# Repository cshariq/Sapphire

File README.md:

<div align="center">

  <h1>Sapphire</h1>
  <p><b>The all-in-one mac app that redefines the notch</b></p>
  <a href="https://sapphire-app.tech" style="text-decoration: none; margin-right: 10px;">
    <div style="background-color: #007aff; color: white; padding: 10px 20px; border-radius: 8px; display: inline-block; font-weight: bold;">
      Official Website
    </div>
  </a>
  <a href="https://github.com/cshariq/Sapphire/releases/latest" style="text-decoration: none;">
    <div style="background-color: #007aff; color: white; padding: 10px 20px; border-radius: 8px; display: inline-block; font-weight: bold;">
      Download Latest Release
    </div>
  </a>
  <a href="https://discord.gg/Ryuea8vM2h" style="text-decoration: none;">
    <div style="background-color: #007aff; color: white; padding: 10px 20px; border-radius: 8px; display: inline-block; font-weight: bold;">
      Join Discord
    </div>
  </a>
</div>

<br>

Sapphire is a sleek notch app that displays current activities neatly around the notch on newer MacBooks. It also includes a suite of convenient features, from nearby share compatibility for easy file transfers to a versatile window snapping system.

## Installation

1.  **Download:** Download the latest package release from the [releases page](https://github.com/cshariq/Sapphire/releases/tag/Latest).
2.  **Install:** Open the downloaded package and follow the installation process.
3.  **Permissions:** On first launch, you may need to grant accessibility and other permissions in `System Settings` for all features to work correctly.

## Features

<div style="display: flex; flex-wrap: wrap; gap: 16px; justify-content: center;">

  <div style="border: 1px solid #30363d; border-radius: 8px; padding: 16px; width: 300px; background-color: #1c1c1e;">
    <h3 style="margin-top: 0;">Nearby Share</h3>
    <p>Allows sharing files, pictures, videos, websites, and more from Android to your mac!</p>
  </div>

  <div style="border: 1px solid #30363d; border-radius: 8px; padding: 16px; width: 300px; background-color: #1c1c1e;">
    <h3 style="margin-top: 0;">Now Playing</h3>
    <p>Displays currently playing media of all types in the notch (works with macOS 15.5 as well), and more.</p>
  </div>

  <div style="border: 1px solid #30363d; border-radius: 8px; padding: 16px; width: 300px; background-color: #1c1c1e;">
    <h3 style="margin-top: 0;">Advanced Audio Features (Beta)</h3>
    <p>Adjust individual app volumes, device volumes, app EQs and device EQs right from the notch</p>
  </div>
  
  <div style="border: 1px solid #30363d; border-radius: 8px; padding: 16px; width: 300px; background-color: #1c1c1e;">
    <h3 style="margin-top: 0;">Eye Break</h3>
    <p>Health should always be your priority. With the sleek notch UI, a reminder is given every 20 minutes to look 20 feet away for 20 seconds, and more.</p>
  </div>

  <div style="border: 1px solid #30363d; border-radius: 8px; padding: 16px; width: 300px; background-color: #1c1c1e;">
    <h3 style="margin-top: 0;">Weather</h3>
    <p>Current weather is persistently shown in the notch, so you're in the know about your surroundings, and more.</p>
  </div>

  <div style="border: 1px solid #30363d; border-radius: 8px; padding: 16px; width: 300px; background-color: #1c1c1e;">
    <h3 style="margin-top: 0;">Gemini</h3>
    <p>Share your screen and discuss topics conveniently using Gemini Live, and more.</p>
  </div>

  <div style="border: 1px solid #30363d; border-radius: 8px; padding: 16px; width: 300px; background-color: #1c1c1e;">
    <h3 style="margin-top: 0;">Calendar</h3>
    <p>See upcoming events and get alerted for ongoing events, and more.</p>
  </div>

  <div style="border: 1px solid #30363d; border-radius: 8px; padding: 16px; width: 300px; background-color: #1c1c1e;">
    <h3 style="margin-top: 0;">Lock Screen</h3>
    <p>See the weather, your music, and upcoming calendar events on your Mac's lockscreen, and more.</p>
  </div>

  <div style="border: 1px solid #30363d; border-radius: 8px; padding: 16px; width: 300px; background-color: #1c1c1e;">
    <h3 style="margin-top: 0;">File Shelf</h3>
    <p>Airdrop and store files conveniently with access to the file shelf, and more.</p>
  </div>

  <div style="border: 1px solid #30363d; border-radius: 8px; padding: 16px; width: 300px; background-color: #1c1c1e;">
    <h3 style="margin-top: 0;">Snap Zones</h3>
    <p>Snapping windows using macOS's built-in snapping tools is limited and leaves a gap between windows. Sapphire provides a versatile and customizable window snapping system, and more.</p>
  </div>

  <div style="border: 1px solid #30363d; border-radius: 8px; padding: 16px; width: 300px; background-color: #1c1c1e;">
    <h3 style="margin-top: 0;">Music</h3>
    <p>View now playing media on the notch with additional information and controls when the now playing media is expanded, and more.</p>
  </div>

  <div style="border: 1px solid #30363d; border-radius: 8px; padding: 16px; width: 300px; background-color: #1c1c1e;">
    <h3 style="margin-top: 0;">Bluetooth</h3>
    <p>Get a notice when a Bluetooth device connects to your Mac, and more.</p>
  </div>

  <div style="border: 1px solid #30363d; border-radius: 8px; padding: 16px; width: 300px; background-color: #1c1c1e;">
    <h3 style="margin-top: 0;">Caffeinate</h3>
    <p>Caffeinate your Mac with a press of a button, and more.</p>
  </div>

</div>

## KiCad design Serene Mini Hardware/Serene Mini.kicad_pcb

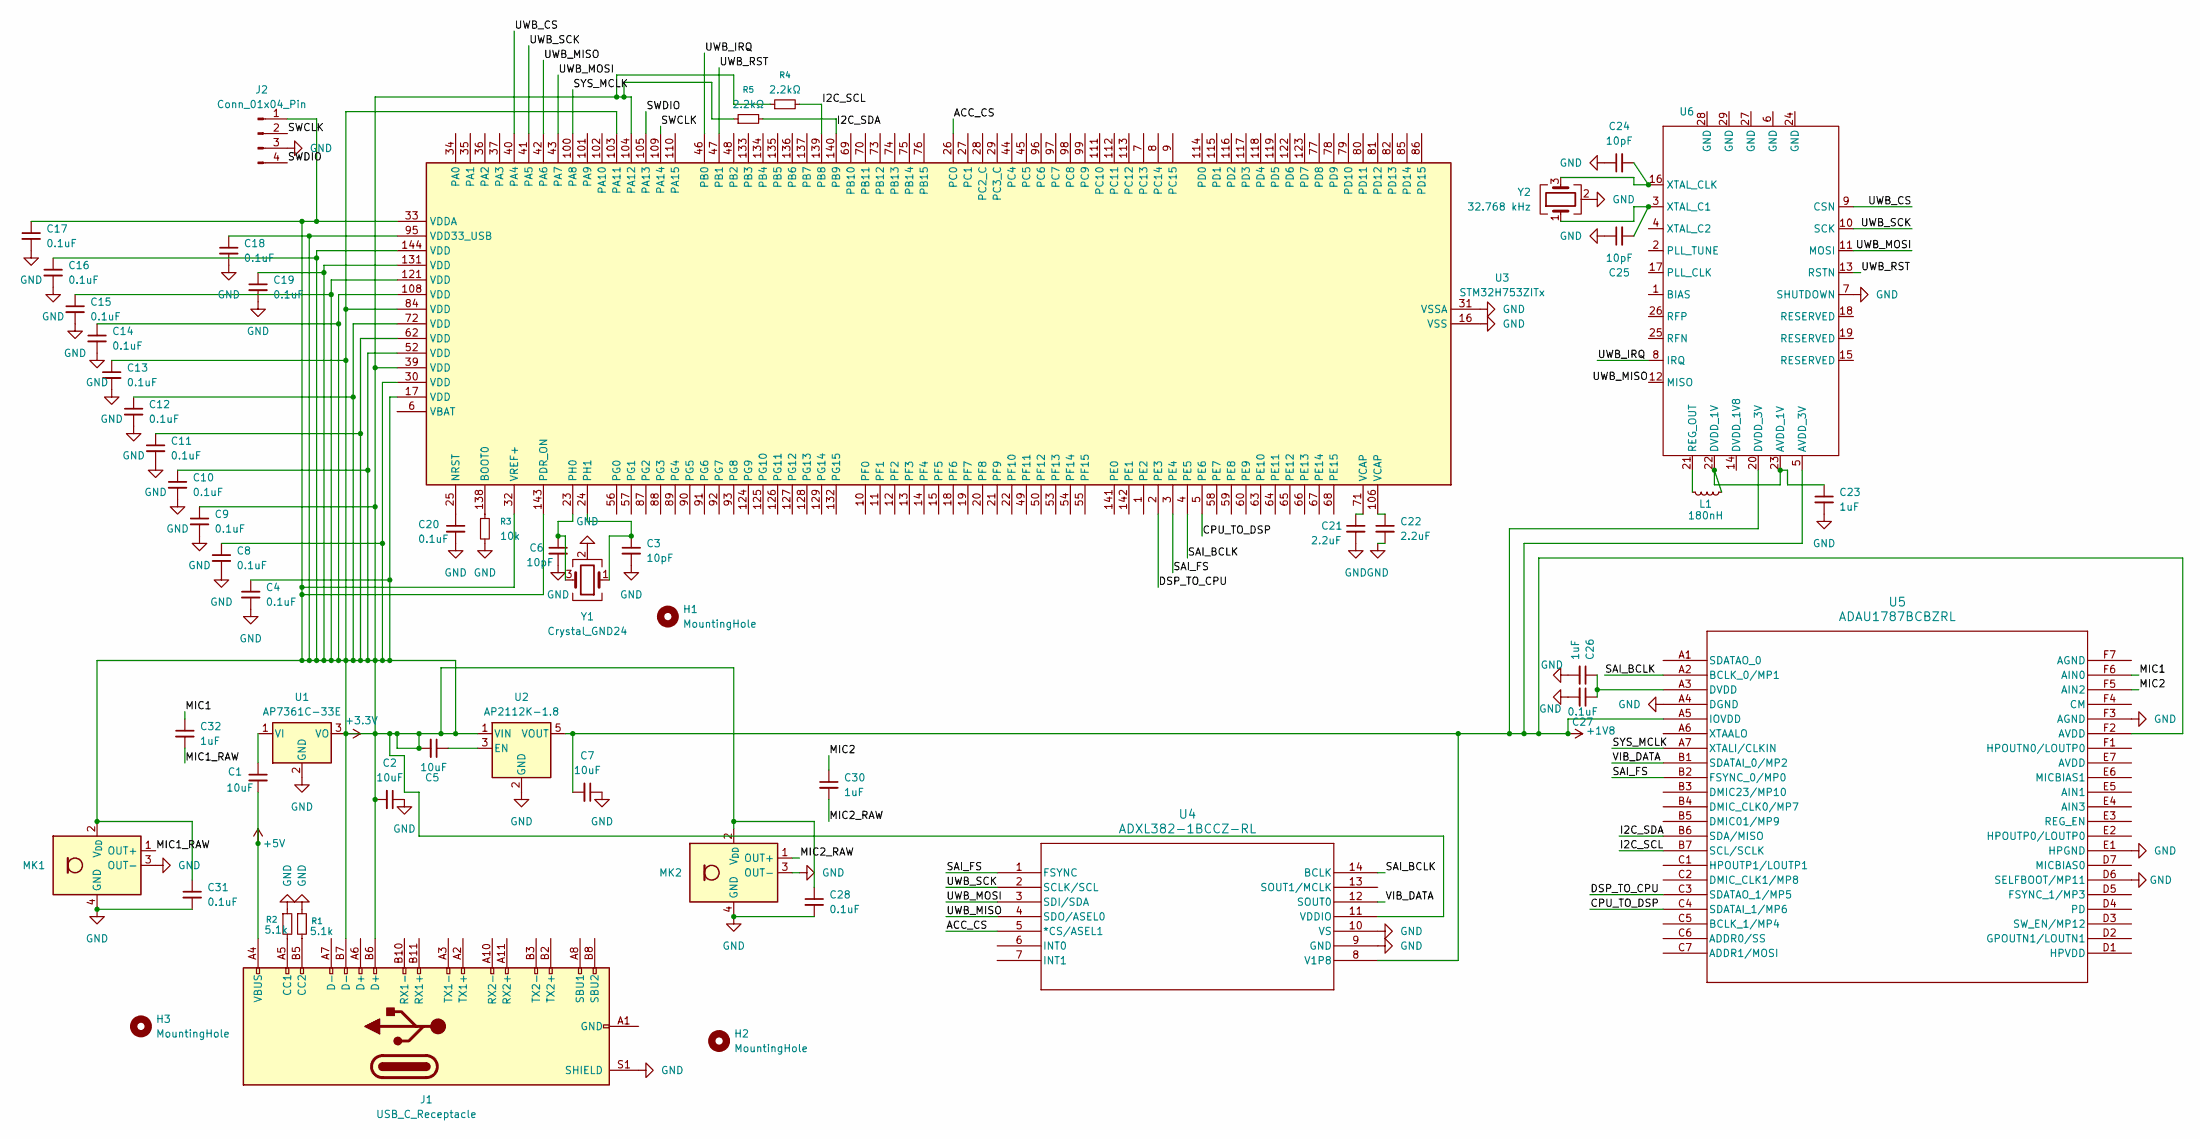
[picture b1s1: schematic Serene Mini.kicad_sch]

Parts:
C1, C2, C5, C7: 10uF; C_0402_1005Metric
C3, C6, C24, C25: 10pF; C_0402_1005Metric
C4, C8, C9, C10, C11, C12, C13, C14, C15, C16, C17, C18, C19, C20, C27, C28, C31: 0.1uF; C_0402_1005Metric
C21, C22: 2.2uF; C_0402_1005Metric
C23, C26, C30, C32: 1uF; C_0402_1005Metric
H1, H2, H3: MountingHole; MountingHole_2.2mm_M2
J1: USB_C_Receptacle; USB_C_Receptacle_Amphenol_12401548E4-2A
J2: Conn_01x04_Pin; PinHeader_1x04_P2.54mm_Vertical
L1: 180nH; L_0603_1608Metric
MK1, MK2: IM73A135V01; Infineon_PG-LLGA-5-2
R1, R2: 5.1k; R_0402_1005Metric
R3: 10k; R_0402_1005Metric
R4, R5: 2.2kΩ; R_0402_1005Metric
U1: AP7361C-33E; SOT-223-3_TabPin2
U2: AP2112K-1.8; SOT-23-5
U3: STM32H753ZITx; LQFP-144_20x20mm_P0.5mm
U4: ADXL382-1BCCZ-RL; ADXL382_Ultralib
U5: ADAU1787BCBZRL; ADAU1787_Ultralib
U6: Spark_SR1020_QFN28
Y1: Crystal_GND24; Crystal_SMD_3225-4Pin_3.2x2.5mm
Y2: 32.768 kHz; Crystal_SMD_3225-4Pin_3.2x2.5mm

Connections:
+1V8: C7.2, U2.5 (VOUT), U4.8 (V1P8), U5.A5 (IOVDD), U5.F2 (AVDD), U6.5 (AVDD_3V), U6.20 (DVDD_3V)
+3.3V: C2.2, C4.1, C5.2, C8.1, C9.1, C10.1, C11.1, C12.1, C13.1, C14.1, C15.1, C16.1, C17.1, C18.1, C19.1, C28.1, C31.1, J1.B6 (D+), J1.B7 (D-), J2.1, MK1.2 (V_{DD}), MK2.2 (V_{DD}), R4.1, R5.1, U1.3 (VO), U2.1 (VIN), U3.17 (VDD), U3.30 (VDD), U3.32 (VREF+), U3.33 (VDDA), U3.39 (VDD), U3.52 (VDD), U3.62 (VDD), U3.72 (VDD), U3.84 (VDD), U3.95 (VDD33_USB), U3.103 (PA11), U3.104 (PA12), U3.108 (VDD), U3.121 (VDD), U3.131 (VDD), U3.143 (PDR_ON), U3.144 (VDD), U4.11 (VDDIO)
+5V: C1.2, J1.A4 (VBUS), J1.A9 (VBUS), J1.B4 (VBUS), J1.B9 (VBUS)
/ACC_CS: U3.26 (PC0), U4.5 (*CS/ASEL1)
/CPU_TO_DSP: U3.5 (PE6), U5.C4 (SDATAI_1/MP6)
/DSP_TO_CPU: U3.2 (PE3), U5.C3 (SDATAO_1/MP5)
/I2C_SCL: R4.2, U3.139 (PB8), U5.B7 (SCL/SCLK)
/I2C_SDA: R5.2, U3.140 (PB9), U5.B6 (SDA/MISO)
/MIC1: C32.1, U5.F6 (AIN0)
/MIC1_RAW: C32.2, MK1.1 (OUT+)
/MIC2: C30.1, U5.F5 (AIN2)
/MIC2_RAW: C30.2, MK2.1 (OUT+)
/SAI_BCLK: U3.4 (PE5), U4.14 (BCLK), U5.A2 (BCLK_0/MP1)
/SAI_FS: U3.3 (PE4), U4.1 (FSYNC), U5.B2 (FSYNC_0/MP0)
/SWCLK: J2.2, U3.109 (PA14)
/SWDIO: J2.4, U3.105 (PA13)
/SYS_MCLK: U3.100 (PA8), U5.A7 (XTALI/CLKIN)
/UWB_CS: U3.40 (PA4), U6.9 (CSN)
/UWB_IRQ: U3.46 (PB0), U6.8 (IRQ)
/UWB_MISO: U3.42 (PA6), U4.4 (SDO/ASEL0), U6.12 (MISO)
/UWB_MOSI: U3.43 (PA7), U4.3 (SDI/SDA), U6.11 (MOSI)
/UWB_RST: U3.47 (PB1), U6.13 (RSTN)
/UWB_SCK: U3.41 (PA5), U4.2 (SCLK/SCL), U6.10 (SCK)
/VIB_DATA: U4.12 (SOUT0), U5.B1 (SDATAI_0/MP2)
GND: C2.1, C3.2, C4.2, C6.2, C7.1, C8.2, C9.2, C10.2, C11.2, C12.2, C13.2, C14.2, C15.2, C16.2, C17.2, C18.2, C19.2, C20.2, C21.2, C22.2, C23.2, C24.1, C25.1, C26.2, C27.2, C28.2, C31.2, J1.S1 (SHIELD), J2.3, MK1.3 (OUT-), MK1.4 (GND), MK1.5 (GND), MK2.3 (OUT-), MK2.4 (GND), MK2.5 (GND), R1.1, R2.1, R3.2, U1.2 (GND), U2.2 (GND), U3.16 (VSS), U3.31 (VSSA), U3.38 (VSS), U3.51 (VSS), U3.61 (VSS), U3.83 (VSS), U3.94 (VSS), U3.107 (VSS), U3.120 (VSS), U3.130 (VSS), U4.9 (GND), U4.10 (VS), U5.A4 (DGND), U5.D6 (SELFBOOT/MP11), U5.E1 (HPGND), U5.F3 (AGND), U6.7 (SHUTDOWN), Y1.2 (G), Y1.4 (G), Y2.2 (G), Y2.4 (G)
unnamed: C21.1, U3.71 (VCAP)
unnamed: C22.1, U3.106 (VCAP)
unnamed: J1.A5 (CC1), R2.2
unnamed: J1.B5 (CC2), R1.2
unnamed: J1.A1 (GND), J1.A12 (GND), J1.B1 (GND), J1.B12 (GND)
unnamed: C1.1, U1.1 (VI)
unnamed: C5.1, U2.3 (EN)
unnamed: R3.1, U3.138 (BOOT0)
unnamed: C20.1, U3.25 (NRST)
unnamed: C6.1, U3.23 (PH0), Y1.3
unnamed: C3.1, U3.24 (PH1), Y1.1
unnamed: C26.1, C27.1, U5.A3 (DVDD)
unnamed: C23.1, L1.1, U6.22 (DVDD_1V), U6.23 (AVDD_1V)
unnamed: L1.2, U6.21 (REG_OUT)
unnamed: C25.2, U6.3 (XTAL_C1), Y2.1
unnamed: C24.2, U6.16 (XTAL_CLK), Y2.3

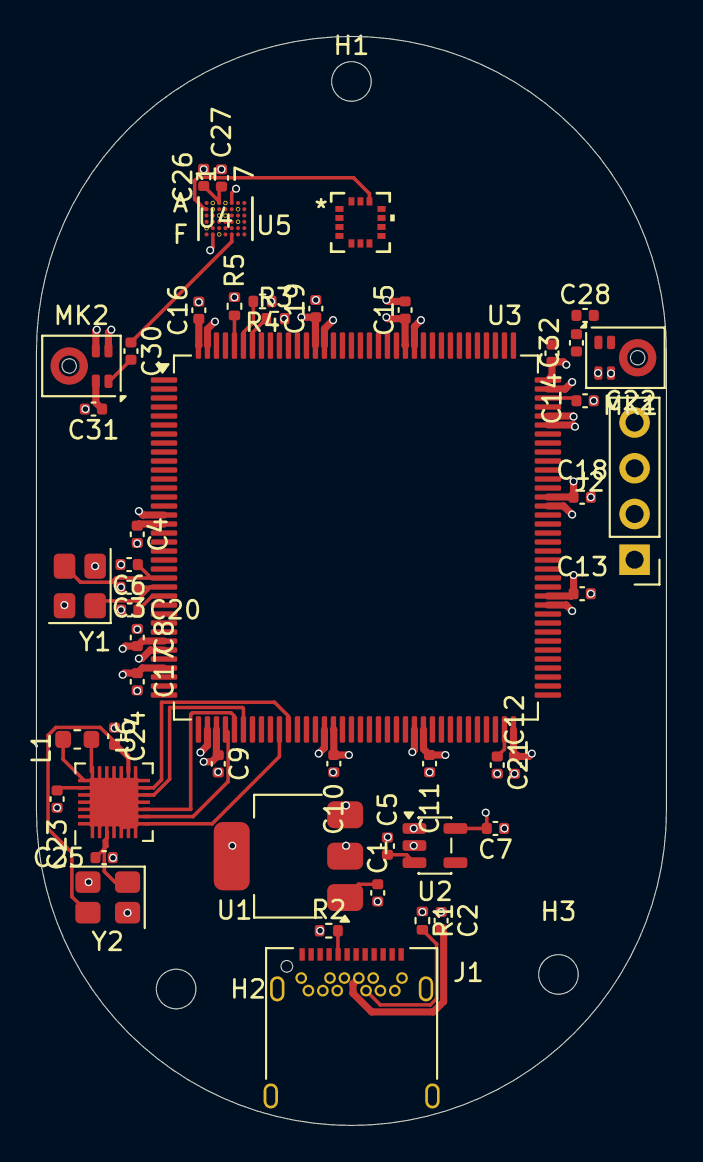
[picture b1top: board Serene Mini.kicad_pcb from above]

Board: 6 copper layers, 35.0 x 60.5 mm, 52 parts (0 on the bottom side), 41 nets.

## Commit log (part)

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2025-09-28 Fix download link for pre-release version in README
2025-09-29 Update issue templates
2025-09-29 Add contributing guidelines to CONTRIBUTING.md
2025-10-07 Initial Release
2025-10-07 Revise README with installation and features details
    Updated README to include installation instructions and detailed feature descriptions.
2025-10-11 Release 0.2
    Features
    - Get verification codes from notification
    - New analytics
    - Battery mini and info widgets on lock screen
    - New pane to declare data collected in onboarding view
    - Disable lock screen widgets during onboarding
2025-10-11 Add internal GoogleService-Info plist file
2025-10-11 Rename GoogleService-Info2.plist to GoogleService-Info.plist
2025-10-11 Add ArcFace mlmodel
2025-10-11 Bug Fixes
    Fixed an issue where notification buttons did not have enough padding
2025-10-11 Bug fixes
2025-10-12 Bug fixes
    - Fixed an issue where gemini doesn't see the current screen
    - Fixed an issue where the device icon wouldn't be visible in system HUD while spotify device was present
    - Fixed an issue where eye break live activity wouldn't work
    - Fixed an issue where after loss of internet or device sleep spotify private api wouldn't work until unless the app was restarted
    And more
2025-10-12 Added Credits
2025-10-12 Rename credits.md to CREDITS.md
2025-10-13 Fix link to Code of Conduct in CONTRIBUTING.md
2025-10-13 Fix link formatting in CONTRIBUTING.md
2025-10-13 Fix links in CONTRIBUTING.md to point to GitHub issues
    Updated links in the CONTRIBUTING.md file to point directly to the GitHub repository issues.
2025-10-13 New XDR display brightness boost
    - The display brightness can now be boosted on devices with certain displays.
    - OpenBubbles support
    - Bug Fixes
2025-10-13 Bug fixed
2025-10-14 Added Crashlytics
2025-10-14 Bug and Formatting Fixes
2025-10-19 Optimize CPU usage: Fix NotchController FPS and download monitoring intervals
    - Fix NotchController FPS logic: Use 60 FPS when idle/showing live activities, 120 FPS only during click-expanded state for widget interactions. Previous logic ran at 120 FPS when idle, wasting CPU/G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
    - Increase DownloadMonitor polling interval from 0.5s to 2.0s (75% reduction)
    - Increase UniversalFileTransferManager polling interval from 0.5s to 1.5s (67% reduction)
    These changes significantly reduce CPU usage during normal operation while maintaining responsive UI.
2025-10-19 Revise security policy and vulnerability reporting
    Updated the security policy to clarify vulnerability reporting.
2025-10-26 New battery management features
2025-11-17 Add GitHub Actions workflow for Xcode build and analyze
2025-11-17 Bug Fixes
    - Fixed an issue where the right sound wouldn't be used when a low battery event occurred
    - Fixed an issue where the settings pane may not focus when opened
2025-11-22 Bug Fixes
    - Fixed an issue with alignment in eye break recommendations pane
    - Optimizations
    - Improved animations
    - Fixed an issue where snap zones preview may be unnecessarily persistent
2025-11-22 Bug Fixes
    - Increased spacing between the info widgets and the clock
2025-11-23 Bug Fixes
    - Fixed an issue where snap zones would remain activated in the background while dropping files
    - Fixed an issue where wrong instructions were given during face id registration
    - Fixed an issue where widgets would unexpectedly close
    - Improved animations while switching between queue and playlists
2025-11-24 Bug Fixes
    - Fixed an issue where menubar auto hide wouldn't work
    - Fixed an issue where always hidden items would be shown even when not in edit mode
    - Fixed an issue where drag file view would appear on drag without the presence of a file when show snap zones on drag was disabled
    - Enhanced snap zones by adding an option to show snap zones instantaneously whenever a window is drag
2026-03-06 Clear API_KEY in GoogleService-Info-Internal.plist
    Removed API_KEY value from GoogleService-Info-Internal.plist.
2026-03-06 Remove API key from GoogleService-Info.plist
    Removed the API key from GoogleService-Info.plist.
2026-03-06 Update README with note on Multi-Audio functionality
    Clarify note about Multi-Audio functionality development.
2026-05-12 Add advanced audio features section to README
2026-06-14 Major Updates and Improvements
    Improvements:
    - Caffeinate feature is now more reliable and can use lid angle to turn off screen when in clamshell mode
    - Now playing is no longer dependent on MediaRemoteAdapter swift package
    - CPU usage reduced by up to 10% when media is playing
    - Volume HUD can now show and allow you to change app volume
    - Improved face id with a lighter more accurate model
2026-06-14 Bug Fixes
    - Improved Install
    - Improved flow for granting disk perm
    - Fixed an issue where onboarding menu would crash when closed
    - Fixed an issue where settings and onboarding menu would open in the background
2026-06-15 Bug Fixes
    - Fixed an issue causing unexpected caffeinate deactivations
    - Fixed an issue with Face ID registration
    - Fixed an issue with weather fetching
    - Fixed an issue with settings and onboarding window level/focus on launch
2026-06-16 Performance Improvements
    - Updated Face ID Model and logic to be significantly more accurate
    - Updated Face ID Model and logic to be significantly faster
    - Updated Spoof detection method to be more accurate
    - Updated MusicManager and NativeMediaController to load info faster
    - Updated MusicManager and NativeMediaController to be more efficient
    Note: macOS 26.5 (or spotify) has an issue with now playing where the track timing may drift overtime. This directly affects the media and lyrics timings in app.
2026-06-18 Efficiency improvements
    - Fixed an issue where moving the cursor system wide would increase the cpu usage
    - Improved hover bounds
2026-06-18 Fix hover detection in hover and click expanded states by expanding interactive window frame and ensuring full mouse event handling
